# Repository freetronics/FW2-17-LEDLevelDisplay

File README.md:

LED Level Display
=================
Copyright 2016 Freetronics Pty Ltd  
Freetronics site:  <www.freetronics.com.au>  
Freetronics email: <info@freetronics.com>  

Based on the project "LED Level Display" described in the book "Funway
Into Electronics Volume 2" by Dick Smith.

Receives an audio level input and displays the strength of the signal
on an LED bargraph.

More information is available at:

  http://www.freetronics.com.au/fw2-level  

INSTALLATION
------------
The design is saved as an EAGLE project. EAGLE PCB design software is
available from www.cadsoftusa.com free for non-commercial use. To use
this project download it and place the directory containing these files
into the "eagle" directory on your computer.

DISTRIBUTION
------------
The specific terms of distribution of this project are governed by the
license referenced below.

LICENSE
-------
Licensed under the TAPR Open Hardware License (www.tapr.org/OHL).
The "license" folder within this repository also contains a copy of
this license in plain text format.

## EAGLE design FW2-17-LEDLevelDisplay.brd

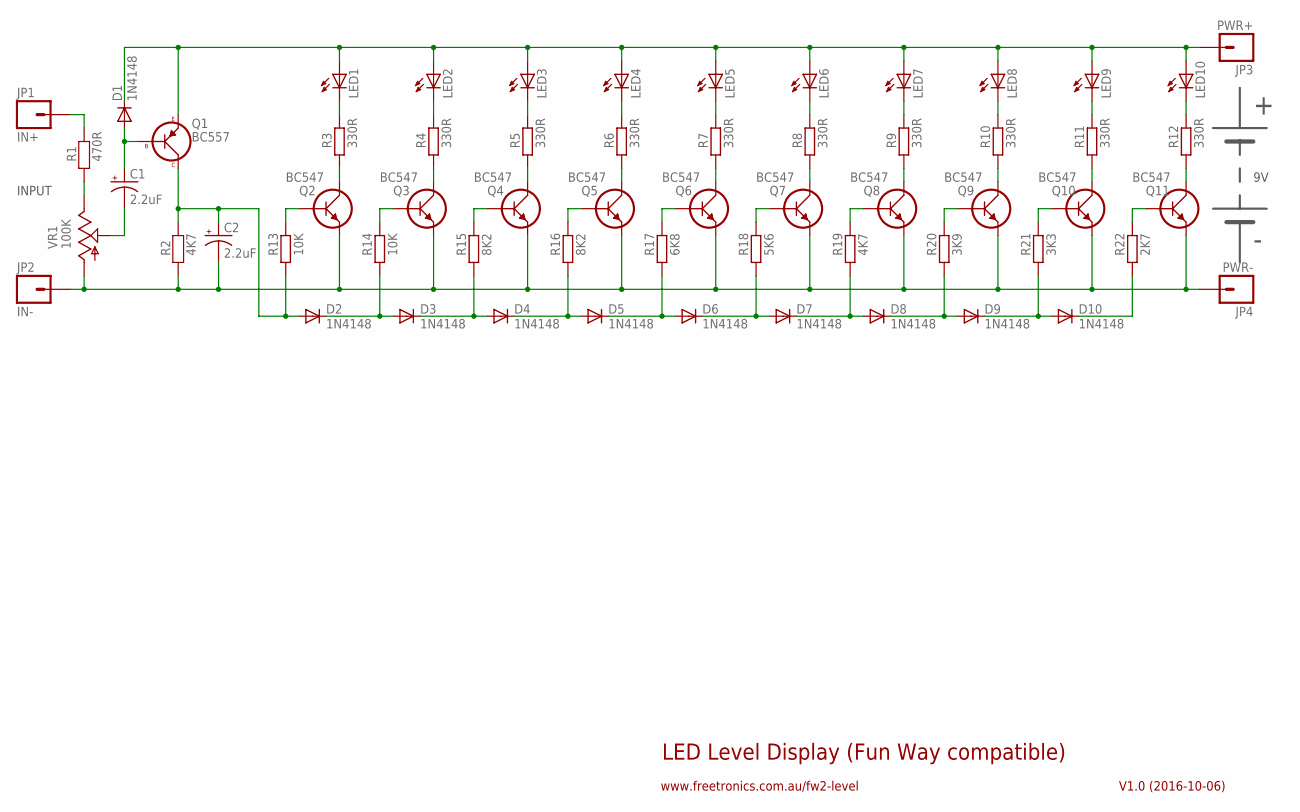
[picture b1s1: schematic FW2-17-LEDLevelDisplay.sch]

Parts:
C1, C2: 2.2uF; CPOL-RADIAL-100UF-25V
D1, D2, D3, D4, D5, D6, D7, D8, D9, D10: 1N4148; DIODE-1N914
JP1: IN+; 1X01
JP2: IN-; 1X01
JP3: PWR+; 1X01
JP4: PWR-; 1X01
LED1, LED2, LED3, LED4, LED5, LED6, LED7, LED8, LED9, LED10: LED5MM
Q1: BC557; TO-92
Q2, Q3, Q4, Q5, Q6, Q7, Q8, Q9, Q10, Q11: BC547; TO-92
R1: 470R; FREETRONICS_AXIAL-0.4
R2: 4K7; FREETRONICS_AXIAL-0.4
R3, R4, R5, R6, R7, R8, R9, R10, R11, R12: 330R; 0309V
R13, R14: 10K; 0309V
R15, R16: 8K2; 0309V
R17: 6K8; 0309V
R18: 5K6; 0309V
R19: 4K7; 0309V
R20: 3K9; 0309V
R21: 3K3; 0309V
R22: 2K7; 0309V
VR1: 100K; 6MM

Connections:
unnamed: D10.C, R22.1
unnamed: Q2.2 (B), R13.2
unnamed: Q2.1 (C), R3.2
unnamed: LED1.K (C), R3.1
unnamed: Q11.2 (B), R22.2
unnamed: D1.C, JP3.1, LED1.A, LED2.A, LED3.A, LED4.A, LED5.A, LED6.A, LED7.A, LED8.A, LED9.A, LED10.A, Q1.3 (E)
unnamed: Q3.1 (C), R4.2
unnamed: LED2.K (C), R4.1
unnamed: Q4.1 (C), R5.2
unnamed: D6.C, D7.A, R18.1
unnamed: LED3.K (C), R5.1
unnamed: Q3.2 (B), R14.2
unnamed: C2.1 (+), D2.A, Q1.1 (C), R2.P$2 (2), R13.1
unnamed: D2.C, D3.A, R14.1
unnamed: C2.2 (-), JP2.1, JP4.1, Q2.3 (E), Q3.3 (E), Q4.3 (E), Q5.3 (E), Q6.3 (E), Q7.3 (E), Q8.3 (E), Q9.3 (E), Q10.3 (E), Q11.3 (E), R2.P$1 (1), VR1.A
unnamed: Q5.1 (C), R6.2
unnamed: LED4.K (C), R6.1
unnamed: Q6.1 (C), R7.2
unnamed: LED5.K (C), R7.1
unnamed: Q7.1 (C), R8.2
unnamed: LED6.K (C), R8.1
unnamed: Q4.2 (B), R15.2
unnamed: Q5.2 (B), R16.2
unnamed: Q6.2 (B), R17.2
unnamed: D5.C, D6.A, R17.1
unnamed: D4.C, D5.A, R16.1
unnamed: D3.C, D4.A, R15.1
unnamed: D7.C, D8.A, R19.1
unnamed: D8.C, D9.A, R20.1
unnamed: D9.C, D10.A, R21.1
unnamed: Q7.2 (B), R18.2
unnamed: Q8.2 (B), R19.2
unnamed: Q9.2 (B), R20.2
unnamed: Q10.2 (B), R21.2
unnamed: Q8.1 (C), R9.2
unnamed: LED7.K (C), R9.1
unnamed: Q9.1 (C), R10.2
unnamed: LED8.K (C), R10.1
unnamed: Q10.1 (C), R11.2
unnamed: LED9.K (C), R11.1
unnamed: Q11.1 (C), R12.2
unnamed: LED10.K (C), R12.1
unnamed: C1.1 (+), D1.A, Q1.2 (B)
unnamed: C1.2 (-), VR1.S
unnamed: R1.P$1 (1), VR1.E
unnamed: JP1.1, R1.P$2 (2)

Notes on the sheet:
LED Level Display (Fun Way compatible)
V1.0 (2016-10-06)
www.freetronics.com.au/fw2-level
INPUT

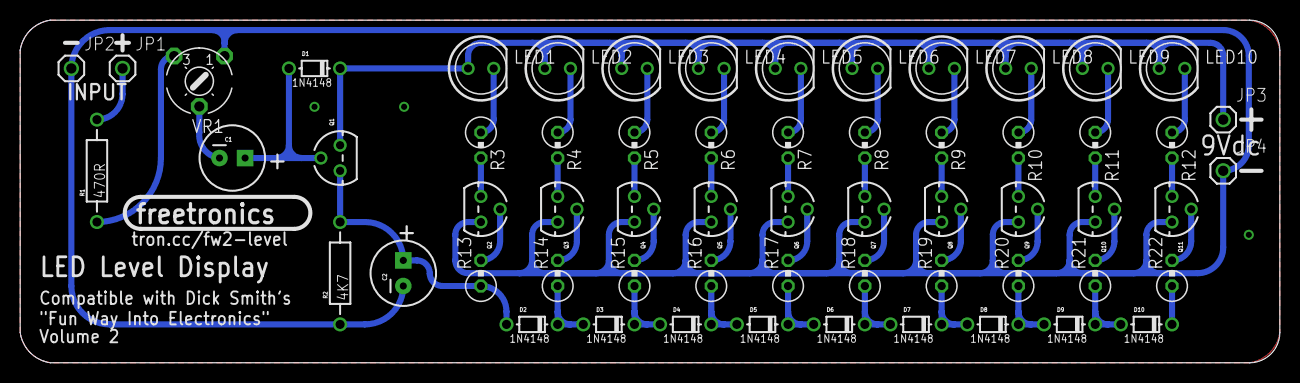
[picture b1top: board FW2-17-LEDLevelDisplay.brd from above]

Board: 2 copper layers, 125.0 x 34.0 mm, 60 parts (0 on the bottom side), 46 nets.

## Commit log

2016-10-06 Initial project import (work in progress)
2016-10-07 Reduced size of diode footprints; fixed part values
2016-10-08 Fixed URL
2016-10-09 Updated silkscreen and labels
2016-10-10 Increased pad size; improved silkscreen

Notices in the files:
FW2-17-LEDLevelDisplay.brd:
(c) 2016 Freetronics Pty Ltd
